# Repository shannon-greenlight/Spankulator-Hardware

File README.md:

# Spankulator-Hardware
The schematics, netlists, etc.
Uses KiCAD
Needs Spankulator-Panel
This version adds separate control of external trigger enable.
Now uses full-width main board.

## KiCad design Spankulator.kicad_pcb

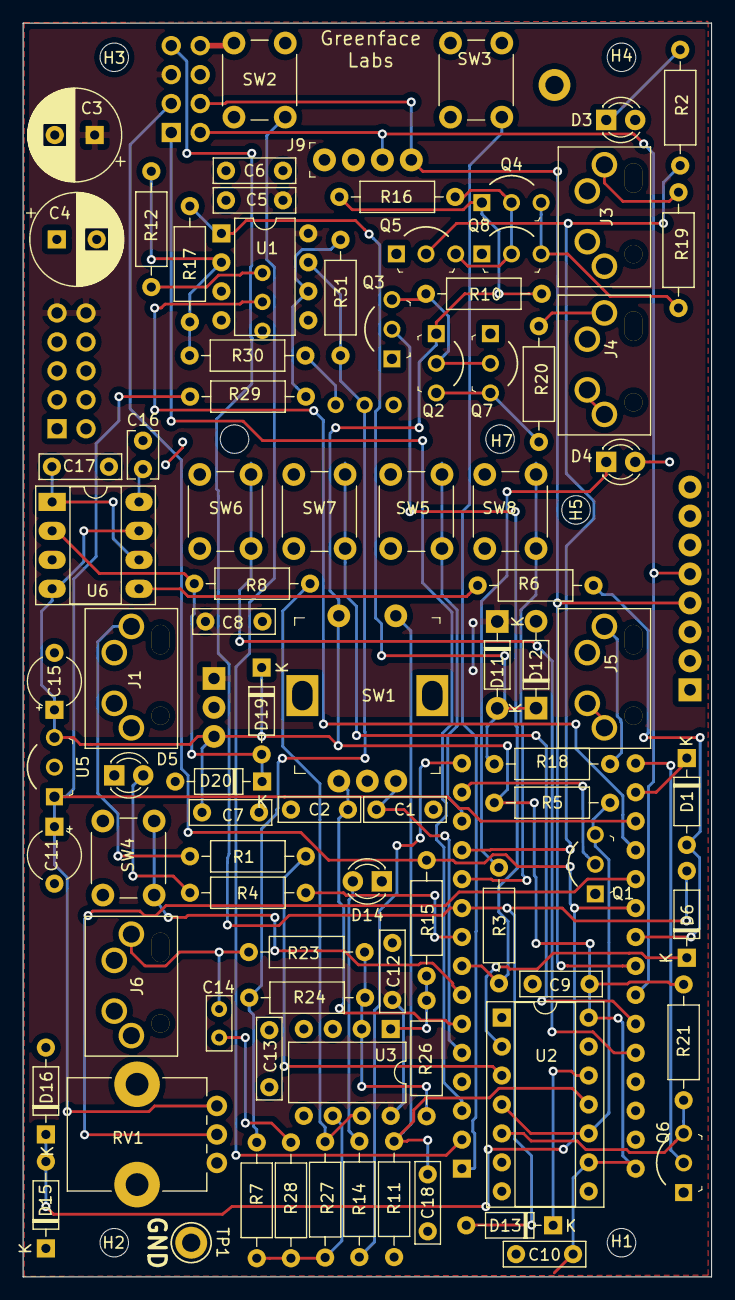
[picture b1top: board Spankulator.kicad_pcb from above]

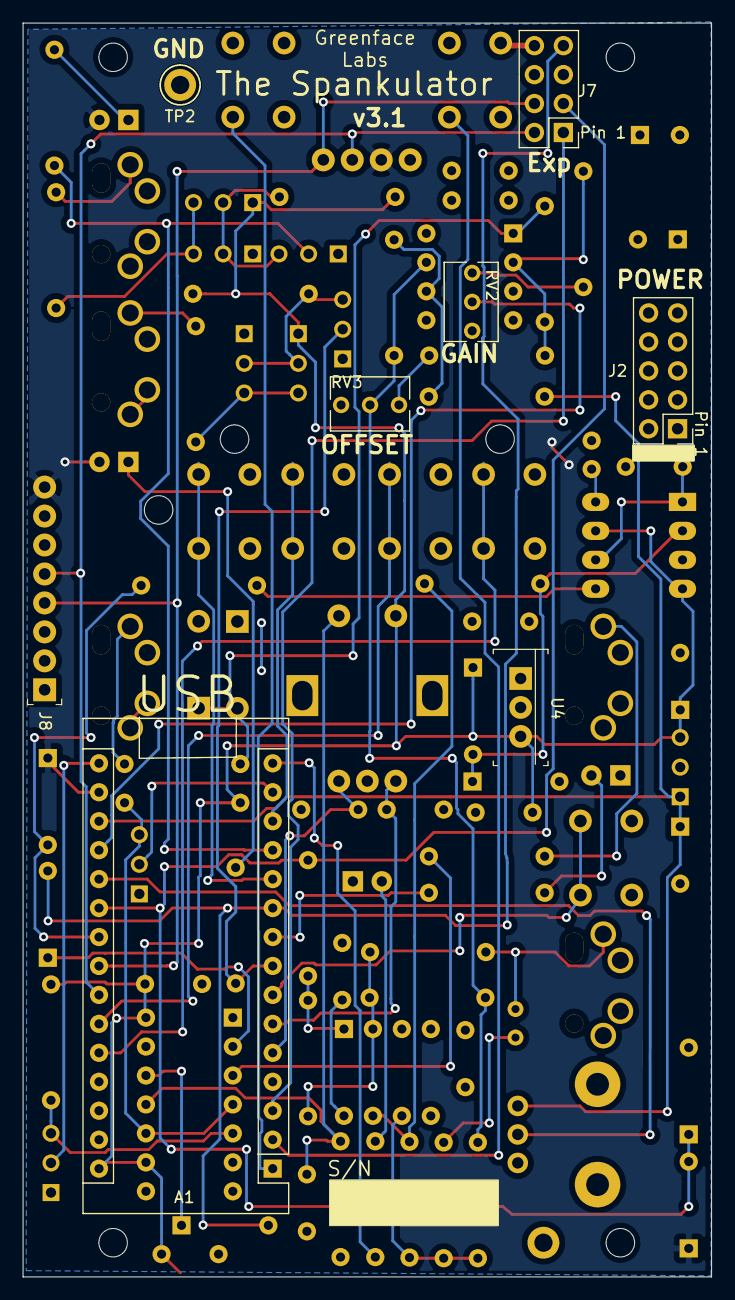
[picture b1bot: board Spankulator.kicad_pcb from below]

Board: 4 copper layers, 60.4 x 110.0 mm, 102 parts (8 on the bottom side), 63 nets.

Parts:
A1: Nano_33IoT; Arduino_Nano
C1, C2, C18: 10nF; C_Rect_L7.0mm_W2.0mm_P5.00mm
C3, C4: 100uF; CP_Radial_D8.0mm_P3.50mm
C5, C6, C7, C9, C12, C13, C17: 100nF; C_Rect_L7.0mm_W2.0mm_P5.00mm
C8, C10: 330nF; C_Rect_L7.0mm_W2.0mm_P5.00mm
C11, C15: 2.2uF; CP_Radial_Tantal_D4.5mm_P5.00mm_Min
C14: 1uF; C_Rect_L4.6mm_W2.0mm_P2.50mm_MKS02_FKP02
C16: 270p; C_Rect_L4.0mm_W2.5mm_P2.50mm
D1, D15, D16, D19, D20: BAT46; D_DO-35_SOD27_P7.62mm_Horizontal
D3: GREEN LED; LED_D3.0mm
D4: BLUE LED; LED_D3.0mm
D5: YELLOW LED; LED_D3.0mm
D6, D13: 1N4148; D_DO-35_SOD27_P7.62mm_Horizontal
D11, D12: SB120; D_DO-41_SOD27_P7.62mm_Horizontal
D14: RED LED; LED_D3.0mm
H1, H2, H3, H4: MountingHole; MountingHole_2.5mm
H5, H6, H7: MountingHole; MountingHole_2.5mm-No-Margin
J1, J3, J4, J5, J6: 3.5mm Jack; Molex-0472570001
J2: 2x5 Header; PinHeader_2x05_P2.54mm_Vertical
J7: Expansion Header; PinHeader_2x04_P2.54mm_Vertical
J8: FRAM Header; PinHeader_1x8_P2.54mm_Drill1.02mm
J9: Display Header; OLED_Header
Q1, Q3, Q5, Q6, Q7, Q8: TN2106; TO-92-3_Formed_Leads
Q2, Q4: VP2106; TO-92-3_Formed_Leads
R1, R5, R6, R8, R11, R15, R21: 10K; R_Axial_DIN0207_L6.3mm_D2.5mm_P10.16mm_Horizontal
R2, R3, R4, R14: 1K; R_Axial_DIN0207_L6.3mm_D2.5mm_P10.16mm_Horizontal
R7, R24, R26, R27, R31: 100K .1%; R_Axial_DIN0207_L6.3mm_D2.5mm_P10.16mm_Horizontal
R10, R16: 100K; R_Axial_DIN0207_L6.3mm_D2.5mm_P10.16mm_Horizontal
R12, R30: 95.3K 1%; R_Axial_DIN0207_L6.3mm_D2.5mm_P10.16mm_Horizontal
R17, R23, R28: 300K .1%; R_Axial_DIN0207_L6.3mm_D2.5mm_P10.16mm_Horizontal
R18, R19, R20: 470; R_Axial_DIN0207_L6.3mm_D2.5mm_P10.16mm_Horizontal
R29: 200K .1%; R_Axial_DIN0207_L6.3mm_D2.5mm_P10.16mm_Horizontal
RV1: 1K; Potentiometer_Bourns_PTV09A-1_Single_Vertical
RV2, RV3: 10K; Potentiometer_Bourns_3266Y_Vertical
SW1: Adj; Rotary_Encoder_Switched_PEC11R
SW2, SW3, SW4, SW5, SW6, SW7, SW8: Push Button; SW_PUSH_6mm
TP1, TP2: TestPoint; TestPoint_Keystone_5005-5009_Compact
U1, U3: TL072; DIP-8_W7.62mm
U2: CD4013BE; DIP-14_W7.62mm_Socket
U4: MC7805CTG; TO-220-3
U5: LP2950-3.3_TO92; TO-92-3_Formed_Leads
U6: MAX7480; DIP-8_W7.62mm_Socket_LongPads

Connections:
3.3VRef: A1.18, C11.1, R29.2, RV1.1, U5.1
+3V3: A1.17, D1.1, D3.2, D4.2, D15.1, J8.8, J9.2
+5V: A1.30, C7.1, C9.1, C10.1, C15.1, D19.1, Q2.1, Q4.1, R5.2, R10.1, R16.1, R21.2, SW1.1, U2.9, U2.14, U4.3, U5.3, U6.4, U6.7
+12V: C3.1, C5.1, C8.1, C12.1, D11.1, J2.9, J2.10, J7.5, U1.8, U3.8, U4.1
-1.65V: R7.2, R24.2, R31.1, RV3.2, U1.7
-12V: C4.2, C6.2, C13.2, D12.2, J2.1, J2.2, J7.6, U1.4, U3.4
/A: A1.6, C2.1, SW1.A
/B: A1.5, C1.1, SW1.B
/Down(v): A1.25, SW7.2
/FXN+: A1.2, SW2.2
/FXN-: A1.1, SW3.2
/Left(<): A1.13, SW5.2
/Right(>): A1.11, SW8.2
/Rpeat: A1.7, SW4.2
/SCL: A1.24, J7.2, J8.5, J9.3
/SDA: A1.23, J7.4, J8.4, J9.4
/Trigger: A1.10, D6.2, D13.2, J7.7
/Up(^): A1.26, SW6.2
GND: A1.4, A1.29, C1.2, C2.2, C3.2, C4.1, C5.2, C6.1, C7.2, C8.2, C9.2, C10.2, C11.2, C12.2, C13.1, C15.2, C16.2, C17.2, C18.2, D5.1, D14.1, D16.2, D20.2, J1.1, J1.3, J1.4, J2.3, J2.4, J2.5, J2.6, J3.1, J3.3, J4.1, J4.3, J5.1, J5.3, J6.1, J6.3, J6.4, J7.8, J8.1, J8.2, J8.7, J9.1, Q1.1, Q3.1, Q5.1, Q6.1, Q7.1, Q8.1, R11.2, RV1.3, SW1.C, SW2.1, SW3.1, SW4.1, SW5.1, SW6.1, SW7.1, SW8.1, TP1.1, TP2.1, U1.3, U1.5, U2.6, U2.7, U2.8, U3.3, U3.5, U4.2, U5.2, U6.3
unnamed: A1.8, Q3.2, R3.1
unnamed: A1.9, R4.1
unnamed: A1.12, Q5.2, R2.1
unnamed: A1.14, Q1.2
unnamed: A1.15, R14.2
unnamed: A1.16, Q6.2
unnamed: A1.19, RV2.2
unnamed: A1.20, RV1.2
unnamed: A1.22, D1.2, R6.2
unnamed: C14.1, J6.2, R23.1
unnamed: C14.2, R28.1
unnamed: C16.1, U6.8
unnamed: C17.1, U6.1, U6.6
unnamed: C18.1, R11.1, SW1.2, U2.11
unnamed: D3.1, R2.2
unnamed: D4.1, R3.2
unnamed: D5.2, R4.2
unnamed: D6.1, U2.2
unnamed: D11.2, D12.1, R17.1, R18.2, U1.1
unnamed: D13.1, U2.12
unnamed: D14.2, R14.1
unnamed: D19.2, D20.1, R8.2, U6.2
unnamed: J1.2, R1.2
unnamed: J3.2, R19.2
unnamed: J4.2, R20.2
unnamed: J5.2, R18.1
unnamed: Q1.3, R5.1, U2.4, U2.10
unnamed: Q2.2, Q3.3, Q7.2, R10.2
unnamed: Q2.3, Q7.3, R20.1
unnamed: Q4.2, Q5.3, Q8.2, R16.2
unnamed: Q4.3, Q8.3, R19.1
unnamed: Q6.3, R21.1, U2.5
unnamed: R1.1, U2.3
unnamed: R6.1, U6.5
unnamed: R12.1, R17.2, R30.1, U1.2
unnamed: R12.2, RV2.3
unnamed: R15.1, R26.2, U3.1
unnamed: R23.2, R24.1, R26.1, U3.2
unnamed: R7.1, R27.1, R28.2, U3.6
unnamed: R8.1, R27.2, U3.7
unnamed: R29.1, R31.2, U1.6
unnamed: R30.2, RV3.3
Reset: A1.3, J7.1
SigIn: A1.21, D15.2, D16.1, J7.3, R15.2

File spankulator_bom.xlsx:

Reference | Quantity | Value | Digi-Key Part
A1 | 1 | Nano_33IoT | 1050-ABX00032-ND
C1 C2 C18 | 3 | 10nF | BC2662CT-ND
C11 C15 | 2 | 2.2uF | 478-12960-1-ND
C14 | 1 | 1uF | 445-180204-ND
C16 | 1 | 270p | BC1018CT-ND
C3 C4 | 2 | 100uF | 1189-3982-ND
C5 C6 C7 C9 C12 C13 C17 | 7 | 100nF | 399-4329-ND
C8 C10 | 2 | 330nF | 445-173597-1-ND
D12 D11 | 2 | SB120 | SB120FSCT-ND
D14 | 1 | RED LED | 732-5005-ND
D20 D19 D16 D15 D1 | 5 | BAT46 | BAT46CT-ND
D3 | 1 | GREEN LED | 732-5008-ND
D4 | 1 | BLUE LED | 732-11401-ND
D5 | 1 | YELLOW LED | 160-1961-ND
D6 D13 | 2 | 1N4148 | 1N4148VSCT-ND
J2 | 1 | 2x5 Header | S2011EC-05-ND
J3 J4 J5 J6 J1 | 5 | 3.5mm Jack | WM17366-ND
J7 | 1 | Expansion Header | S2011EC-04-ND
J8 | 1 | FRAM Header | 1212-1097-ND
J9 | 1 | Display Header | SAM1011-04-ND
Q1 Q6 Q5 Q3 Q7 Q8 | 6 | TN2106 | TN2106N3-G-ND
Q2 Q4 | 2 | VP2106 | VP2106N3-G-ND
R1 R15 R11 R5 R8 R21 R6 | 7 | 10K | CF14JT10K0CT-ND
R10 R16 | 2 | 100K | CF14JT100KCT-ND
R17 R23 R28 | 3 | 300K .1% | RN55E3003BB14-ND
R19 R18 R20 | 3 | 470 | PPC470W-1CT-ND
R2 R4 R3 R14 | 4 | 1K | CF14JT1K00CT-ND
R24 R26 R27 R31 R7 | 5 | 100K .1% | A105968CT-ND
R29 | 1 | 200K .1% | CMF200KHCCT-ND
R30 R12 | 2 | 95.3K 1% | CMF95.3KQFCT-ND
RV1 | 1 | 1K | PTV09A-4225F-B102-ND
RV2 RV3 | 2 | 10K | 490-2875-ND
SW1 | 1 | Adj | PEC12R-4230F-S0024-ND
SW5 SW4 SW3 SW2 SW7 SW6 SW8 | 7 | Push Button | 450-1643-ND
TP1 TP2 | 2 | TestPoint | 36-5006-ND
U1 U3 | 2 | TL072 | 296-14997-5-ND
U2 | 1 | CD4013BE | 296-2033-5-ND
U4 | 1 | MC7805CTG | MC7805CTGOS-ND
U5 | 1 | LP2950-3.3_TO92 | 296-31455-1-ND
U6 | 1 | MAX7480 | MAX7480EPA+-ND
J10 | 1 | FRAM Pins | 732-5321-ND
J11 | 1 | OLED Pins | 732-5317-ND
J12 | 1 | Eurorack Power Cable | H3CCS-1618G-ND
J13 J14 | 2 | Arduino Socket | S7048-ND
KN1 | 1 | Selector Knob | 226-4215-ND
KN2 | 1 | Scale Knob | 1722-1241-ND
M1 | 1 | FRAM_Module | 1528-1035-ND
M2 | 1 | OLED_Module |  | https://www.amazon.com/gp/product/B072Q2X2LL/
N1 N2 N3 N4 N5 N6 N7 | 7 | Nut | 36-4687-ND
SC1 SC2 SC3 SC4 SC5 | 5 | Nylon Screw | 36-29331-ND
SC6 SC7 SC8 SC9 | 4 | Mounting Screw | 335-1156-ND
SK1 SK2 | 2 | A_08-LC-TT | AE9986-ND
SK3 | 1 | A_14-LC-TT | AE9989-ND
SO1 SO2 SO3 SO4 | 4 | Standoff 12mm | 732-13063-ND
SO5 SO6 SO7 | 3 | Standoff 11mm | 732-13059-ND
W1 W2 W3 W4 | 4 | Washer | RPC3448-ND

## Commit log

2020-08-17 Added more files
2020-08-17 Adds display to assembly instructions.
2020-08-17 Adds PDF of schematic
2020-08-17 Adds missing parts to BOM
2020-08-19 Adds spice files
2020-11-07 v2.2.3
2020-11-22 This version adds separate control of external trigger enable. Now uses full-width main board.
2020-11-22 Removes gerber.zip
2021-01-24 Ver. 2.3
2021-01-24 Ver 2.3
2021-02-03 Adds needed parts.
2021-02-09 Added Eurorack mounting screws
2021-03-04 ver 3.0
2021-05-21 Version 3.1
    Adds adjustment pots.
